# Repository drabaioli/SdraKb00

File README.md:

# SdraKb00

12 keys hot-swap macropad with rotary encoder.

## Assembled images

## Features

- 11 hot-swap keys
- Rotary encoder with push button
- AtMega32U4 MCU
- Per-key RGB led for backlighting
- USB-C connector
- On PCB SPI header
- MCU reset button
- Switch mounting plate
- Power LED indicator

## Keyboard Layout Editor link

[](http://www.keyboard-layout-editor.com/##@_backcolor=%23101C24&name=SdraKb00&author=drabaioli&switchMount=cherry&switchBrand=gateron&switchType=KS-3-Red&plate:true&pcb:false%3B&@_c=%23101C24&t=%2388FB7A%3B&=%3Ci%20class%2F='fa%20fa-fast-backward'%3E%3C%2F%2Fi%3E&=%3Ci%20class%2F='fa%20fa-play'%3E%3C%2F%2Fi%3E&=%3Ci%20class%2F='fa%20fa-fast-forward'%3E%3C%2F%2Fi%3E&_a:7&f:9%3B&=%3Ci%20class%2F='fa%20fa-circle-o-notch'%3E%3C%2F%2Fi%3E%3B&@_f:3%3B&=&=&=&_c=%2388FB7A&t=%23101C24%3B&=%3B&@_c=%23101C24&t=%2388FB7A&a:4%3B&=%3Ci%20class%2F='fa%20fa-chrome'%3E%3C%2F%2Fi%3E&=%3Ci%20class%2F='fa%20fa-terminal'%3E%3C%2F%2Fi%3E&=%3Ci%20class%2F='fa%20fa-youtube-play'%3E%3C%2F%2Fi%3E&=%3Ci%20class%2F='fa%20fa-spotify'%3E%3C%2F%2Fi%3E)

## Schematic

## PCB

## Switch plate

## Production files

The [production/](production/) folder contains files required for manufacturing the board, namely the [SdraKb00.zip](production/SdraKb00.zip) is an export (JLCPCB accepted format) of the gerber files and the [BOM](production/SdraKb00_bom.csv). The BOM was edited to add links to JLCPCB parts. Both files can be used to get the PCB manufactured by [JLCPCB](https://jlcpcb.com/) with relative components.

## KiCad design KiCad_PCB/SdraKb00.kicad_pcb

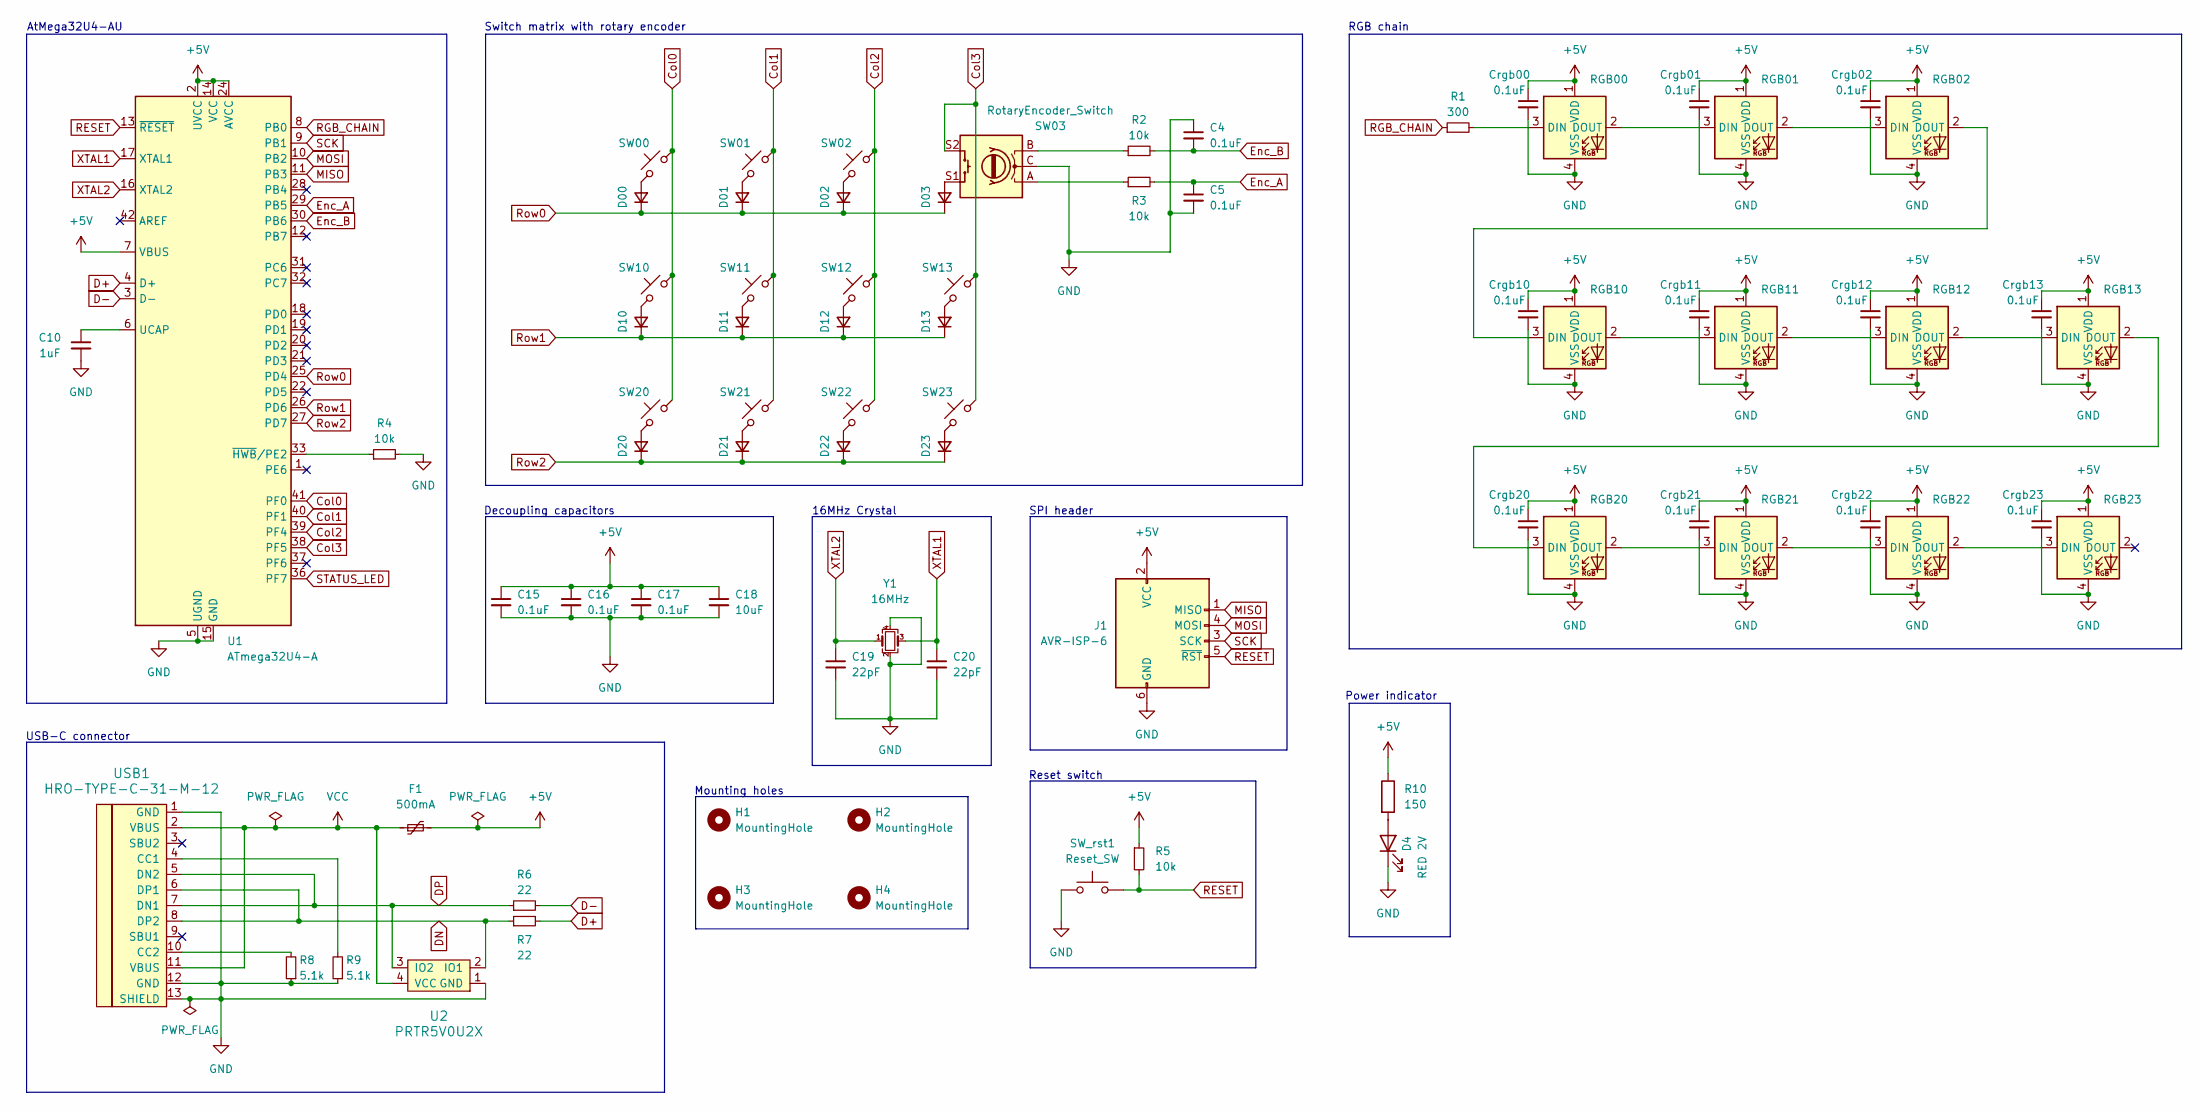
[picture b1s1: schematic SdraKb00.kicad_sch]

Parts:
C4, C5, C15, C16, C17: 0.1uF; C_0805_2012Metric_Pad1.18x1.45mm_HandSolder
C10: 1uF; C_0805_2012Metric_Pad1.18x1.45mm_HandSolder
C18: 10uF; C_0805_2012Metric_Pad1.18x1.45mm_HandSolder
C19, C20: 22pF; C_0805_2012Metric_Pad1.18x1.45mm_HandSolder
Crgb00, Crgb01, Crgb02, Crgb10, Crgb11, Crgb12, Crgb13, Crgb20, Crgb21, Crgb22, Crgb23: 0.1uF; C_0805_2012Metric_Pad1.18x1.45mm_HandSolder
D00, D01, D02, D03, D10, D11, D12, D13, D20, D21, D22, D23: D_Small; D_SOD-123
D4: RED 2V; LED_1206_3216Metric_Pad1.42x1.75mm_HandSolder
F1: 500mA; Fuse_1206_3216Metric_Pad1.42x1.75mm_HandSolder
H1, H2, H3, H4: MountingHole; MountingHole_3.2mm_M3
J1: AVR-ISP-6; PinHeader_1x06_P2.00mm_Horizontal
R1: 300; R_0805_2012Metric_Pad1.20x1.40mm_HandSolder
R2, R3, R4, R5: 10k; R_0805_2012Metric_Pad1.20x1.40mm_HandSolder
R6, R7: 22; R_0805_2012Metric_Pad1.20x1.40mm_HandSolder
R8, R9: 5.1k; R_0805_2012Metric_Pad1.20x1.40mm_HandSolder
R10: 150; R_0805_2012Metric_Pad1.20x1.40mm_HandSolder
RGB00, RGB01, RGB02, RGB10, RGB11, RGB12, RGB13, RGB20, RGB21, RGB22, RGB23: MX_SK6812MINI-E; LED_MX_6028R-ROT
SW00, SW01, SW02, SW10, SW11, SW12, SW13, SW20, SW21, SW22, SW23: SW_Push_45deg; SW_MX_HS_CPG151101S11_1u
SW03: RotaryEncoder_Switch; ROT_Alps_EC11E-Switch
SW_rst1: Reset_SW; SW_SPST_SKQG_WithStem
U1: ATmega32U4-A; TQFP-44_10x10mm_P0.8mm
U2: PRTR5V0U2X; SOT-143_Handsoldering
USB1: HRO-TYPE-C-31-M-12; HRO-TYPE-C-31-M-12-HandSoldering
Y1: 16MHz; Crystal_SMD_3225-4Pin_3.2x2.5mm_HandSoldering

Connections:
+5V: C15.1, C16.1, C17.1, C18.1, Crgb00.1, Crgb01.1, Crgb02.1, Crgb10.1, Crgb11.1, Crgb12.1, Crgb13.1, Crgb20.1, Crgb21.1, Crgb22.1, Crgb23.1, F1.2, J1.2 (VCC), R5.1, R10.1, RGB00.1 (VDD), RGB01.1 (VDD), RGB02.1 (VDD), RGB10.1 (VDD), RGB11.1 (VDD), RGB12.1 (VDD), RGB13.1 (VDD), RGB20.1 (VDD), RGB21.1 (VDD), RGB22.1 (VDD), RGB23.1 (VDD), U1.2 (UVCC), U1.7 (VBUS), U1.14 (VCC), U1.24 (AVCC), U1.34 (VCC), U1.44 (AVCC)
Col0: SW00.2, SW10.2, SW20.2, U1.41 (PF0)
Col1: SW01.2, SW11.2, SW21.2, U1.40 (PF1)
Col2: SW02.2, SW12.2, SW22.2, U1.39 (PF4)
Col3: SW03.S2, SW13.2, SW23.2, U1.38 (PF5)
D+: R7.2, U1.4 (D+)
D-: R6.2, U1.3 (D-)
DN: R7.1, U2.2 (IO1), USB1.6 (DP1), USB1.8 (DP2)
DP: R6.1, U2.3 (IO2), USB1.5 (DN2), USB1.7 (DN1)
Enc_A: C5.1, R3.2, U1.29 (PB5)
Enc_B: C4.2, R2.2, U1.30 (PB6)
GND: C4.1, C5.2, C10.2, C15.2, C16.2, C17.2, C18.2, C19.2, C20.2, Crgb00.2, Crgb01.2, Crgb02.2, Crgb10.2, Crgb11.2, Crgb12.2, Crgb13.2, Crgb20.2, Crgb21.2, Crgb22.2, Crgb23.2, D4.1 (K), J1.6 (GND), R4.2, R8.1, R9.1, RGB00.4 (VSS), RGB01.4 (VSS), RGB02.4 (VSS), RGB10.4 (VSS), RGB11.4 (VSS), RGB12.4 (VSS), RGB13.4 (VSS), RGB20.4 (VSS), RGB21.4 (VSS), RGB22.4 (VSS), RGB23.4 (VSS), SW03.C, SW_rst1.1, U1.5 (UGND), U1.15 (GND), U1.23 (GND), U1.35 (GND), U1.43 (GND), U2.1 (GND), USB1.1 (GND), USB1.12 (GND), USB1.13 (SHIELD), Y1.2, Y1.4
MISO: J1.1 (MISO), U1.11 (PB3)
MOSI: J1.4 (MOSI), U1.10 (PB2)
unnamed: D00.2 (A), SW00.1
unnamed: D01.2 (A), SW01.1
unnamed: D02.2 (A), SW02.1
unnamed: D03.2 (A), SW03.S1
unnamed: D4.2 (A), R10.2
unnamed: D10.2 (A), SW10.1
unnamed: D11.2 (A), SW11.1
unnamed: D12.2 (A), SW12.1
unnamed: D13.2 (A), SW13.1
unnamed: D20.2 (A), SW20.1
unnamed: D21.2 (A), SW21.1
unnamed: D22.2 (A), SW22.1
unnamed: D23.2 (A), SW23.1
unnamed: R2.1, SW03.B
unnamed: R3.1, SW03.A
unnamed: R1.2, RGB00.3 (DIN)
unnamed: RGB00.2 (DOUT), RGB01.3 (DIN)
unnamed: RGB01.2 (DOUT), RGB02.3 (DIN)
unnamed: RGB02.2 (DOUT), RGB10.3 (DIN)
unnamed: RGB10.2 (DOUT), RGB11.3 (DIN)
unnamed: RGB11.2 (DOUT), RGB12.3 (DIN)
unnamed: RGB12.2 (DOUT), RGB13.3 (DIN)
unnamed: RGB13.2 (DOUT), RGB20.3 (DIN)
unnamed: RGB20.2 (DOUT), RGB21.3 (DIN)
unnamed: RGB21.2 (DOUT), RGB22.3 (DIN)
unnamed: RGB22.2 (DOUT), RGB23.3 (DIN)
unnamed: C10.1, U1.6 (UCAP)
unnamed: R4.1, U1.33 (~HWB/PE2)
unnamed: R9.2, USB1.4 (CC1)
unnamed: R8.2, USB1.10 (CC2)
RESET: J1.5 (~RST), R5.2, SW_rst1.2, U1.13 (~RESET)
RGB_CHAIN: R1.1, U1.8 (PB0)
Row0: D00.1 (K), D01.1 (K), D02.1 (K), D03.1 (K), U1.25 (PD4)
Row1: D10.1 (K), D11.1 (K), D12.1 (K), D13.1 (K), U1.26 (PD6)
Row2: D20.1 (K), D21.1 (K), D22.1 (K), D23.1 (K), U1.27 (PD7)
SCK: J1.3 (SCK), U1.9 (PB1)
STATUS_LED: U1.36 (PF7)
VCC: F1.1, U2.4 (VCC), USB1.2 (VBUS), USB1.11 (VBUS)
XTAL1: C20.1, U1.17 (XTAL1), Y1.3
XTAL2: C19.1, U1.16 (XTAL2), Y1.1

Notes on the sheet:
USB-C connector
RGB chain
Reset switch
Mounting holes
Power indicator
SPI header
AtMega32U4-AU
Switch matrix with rotary encoder
16MHz Crystal
Decoupling capacitors

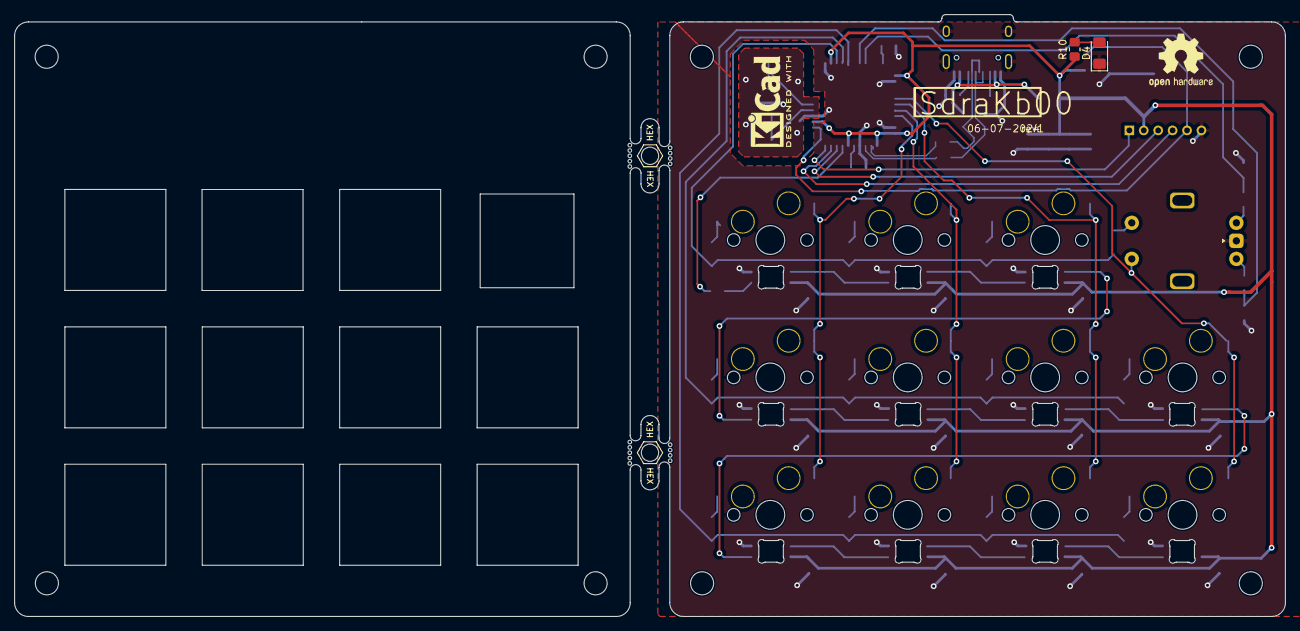
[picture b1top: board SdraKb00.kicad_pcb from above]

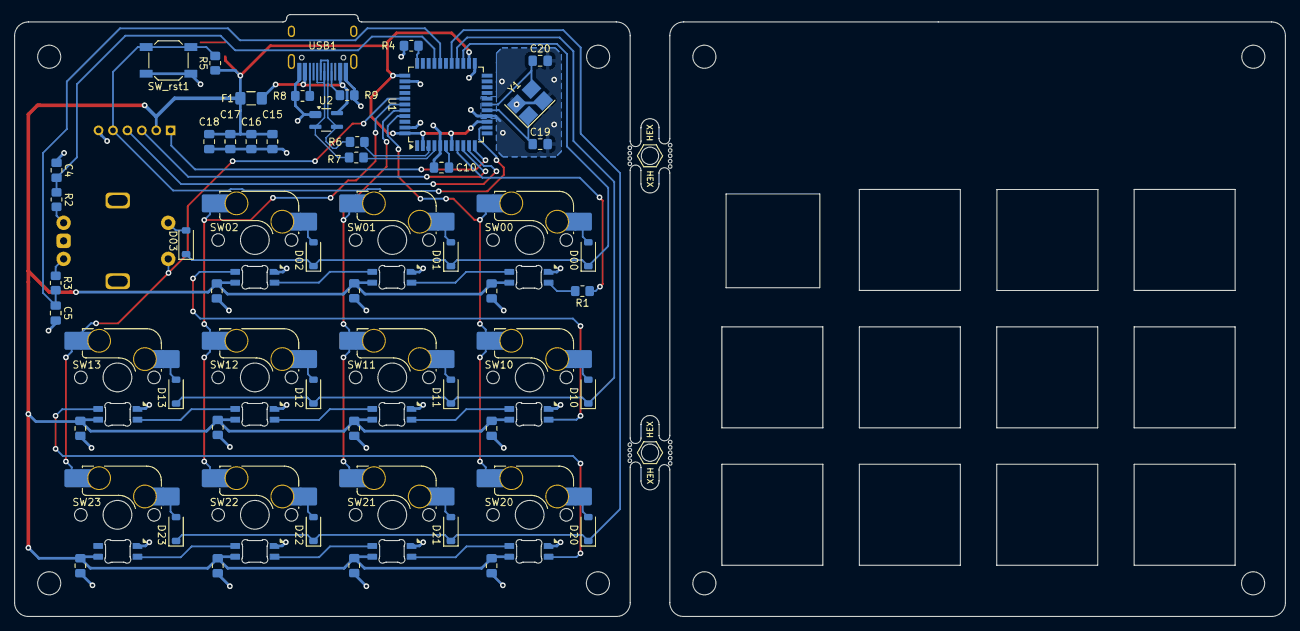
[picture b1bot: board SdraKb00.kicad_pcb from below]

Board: 2 copper layers, 176.1 x 83.4 mm, 95 parts (80 on the bottom side), 53 nets.

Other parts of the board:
H5, H6, H7, H8: MountingHole; MountingHole_3.2mm_M3
MB5, MB5#2: 5.5mm; mousebites_5p5mm_easysnap
SW00_cutout, SW01_cutout, SW02_cutout, SW10_cutout, SW11_cutout, SW12_cutout, SW13_cutout, SW20_cutout, SW21_cutout, SW22_cutout, SW23_cutout: SW_Push_45deg; SW_MX_HS_CPG151101S11_1u
SW03_cutout: RotaryEncoder_Switch; ROT_Alps_EC11E-Switch

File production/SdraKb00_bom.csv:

Id,Designator,Footprint,Quantity,Designation,Supplier and ref,Comment,LCSC link
1,R10,R_0805_2012Metric_Pad1.20x1.40mm_HandSolder,1,150,C410057,,https://www.lcsc.com/product-detail/Chip-Resistor-Surface-Mo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
2,SW03,ROT_Alps_EC11E-Switch,1,RotaryEncoder_Switch,C470742,,https://www.lcsc.com/product-detail/Rotary-Encoders_ALPSALPI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
3,D4,LED_1206_3216Metric_Pad1.42x1.75mm_HandSolder,1,RED 2V,C125086,,https://www.lcsc.com/product-detail/span-style-background-co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
4,J1,PinHeader_1x06_P2.00mm_Horizontal,1,AVR-ISP-6,C707009,,https://www.lcsc.com/product-detail/span-style-background-co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
5,"D20,D12,D01,D22,D03,D10,D02,D23,D21,D13,D00,D11",D_SOD-123,12,D_Small,C77978,,https://www.lcsc.com/product-detail/Switching-Diodes_MCC-Mic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
5,"SW22,SW01,SW01,SW01,SW01,SW01,SW01,SW12,SW11,SW01,SW13,SW01,SW20,SW23,SW01,SW01,SW01,SW10,SW01,SW02,SW21,SW00",SW_MX_HS_CPG151101S11_1u,11,SW_Push_45deg,C2803348,,https://www.lcsc.com/product-detail/Mechanical-Keyboard-Shaf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
7,"RGB22,RGB01,RGB21,RGB00,RGB11,RGB20,RGB10,RGB13,RGB02,RGB12,RGB23",LED_MX_6028R-ROT,11,MX_SK6812MINI-E,C5149201,,https://www.lcsc.com/product-detail/RGB-LEDs-Built-in-IC_OPS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
8,"Crgb23,C15,Crgb11,Crgb21,C4,Crgb00,Crgb13,Crgb22,C5,Crgb12,Crgb10,Crgb20,Crgb02,C17,Crgb01,C16",C_0805_2012Metric_Pad1.18x1.45mm_HandSolder,16,0.1uF,C730460,,https://www.lcsc.com/product-detail/Multilayer-Ceramic-Capac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
9,"C20,C19",C_0805_2012Metric_Pad1.18x1.45mm_HandSolder,2,22pF,C472837,,https://www.lcsc.com/product-detail/Multilayer-Ceramic-Capac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
10,"R6,R7",R_0805_2012Metric_Pad1.20x1.40mm_HandSolder,2,22,C413152,,https://www.lcsc.com/product-detail/Chip-Resistor-Surface-Mo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
11,F1,Fuse_1206_3216Metric_Pad1.42x1.75mm_HandSolder,1,500mA,C883126,,https://www.lcsc.com/product-detail/Resettable-Fuses_BHFUSE-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
12,"R8,R9",R_0805_2012Metric_Pad1.20x1.40mm_HandSolder,2,5.1k,C230649,,https://www.lcsc.com/product-detail/Chip-Resistor-Surface-Mo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
13,"R5,R4,R2,R3",R_0805_2012Metric_Pad1.20x1.40mm_HandSolder,4,10k,C180849,,https://www.lcsc.com/product-detail/Chip-Resistor-Surface-Mo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
14,C10,C_0805_2012Metric_Pad1.18x1.45mm_HandSolder,1,1uF,C2798196,,https://www.lcsc.com/product-detail/Multilayer-Ceramic-Capac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
15,Y1,Crystal_SMD_3225-4Pin_3.2x2.5mm_HandSoldering,1,16MHz,C5380579,,https://www.lcsc.com/product-detail/Crystals_JGHC-S321600022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
16,C18,C_0805_2012Metric_Pad1.18x1.45mm_HandSolder,1,10uF,C95841,,https://www.lcsc.com/product-detail/Multilayer-Ceramic-Capac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
17,SW_rst1,SW_SPST_SKQG_WithStem,1,Reset_SW,C116647,,https://www.lcsc.com/product-detail/Tactile-Switches_ALPSALP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
18,R1,R_0805_2012Metric_Pad1.20x1.40mm_HandSolder,1,300,C413174,,https://www.lcsc.com/product-detail/Chip-Resistor-Surface-Mo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
19,U1,TQFP-44_10x10mm_P0.8mm,1,ATmega32U4-A,C44854,,https://www.lcsc.com/product-detail/Microcontrollers-MCU-MPU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
20,USB1,HRO-TYPE-C-31-M-12-HandSoldering,1,HRO-TYPE-C-31-M-12,C165948,,https://www.lcsc.com/product-detail/USB-Type-C_Korean-Hropar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
21,U2,SOT-143_Handsoldering,1,PRTR5V0U2X,C5375321,,https://www.lcsc.com/product-detail/ESD-and-Surge-Protection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

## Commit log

2024-05-04 Setup project and submodules.
2024-05-10 Initial sketch based on jeremypaton (see link below)
    https://www.jeremypaton.com/2021/04/20/designing-a-custom-keyboard-pt-1/
2024-05-10 Ignoring KiCad tmp files.
2024-05-10 Ignoring KiCad tmp files. (#1)
2024-05-10 Fixing library paths.
2024-05-10 Adjusted first sketch based on masterzen.
    https://www.masterzen.fr/2020/05/03/designing-a-keyboard-part-1/
2024-05-10 Adding layout image to readme.
2024-05-12 Replaced AtMega32U4 with default library. Adding switch array.
2024-05-12 Adding RGB chain.
2024-05-12 Adding mounting holes.
2024-05-12 Readme.
2024-05-12 Repo setup (#2)
    * Setup project and submodules.
    * Initial sketch based on jeremypaton (see link below)
    https://www.jeremypaton.com/2021/04/20/designing-a-custom-keyboard-pt-1/
    * Fixing library paths.
    * Adjusted first sketch based on masterzen.
    https://www.masterzen.fr/2020/05/03/designing-a-keyboard-part-1/
2024-05-14 First round assigning footprints.
2024-05-19 Complete footprint assignment.
    - Removed unused submodules
    - Adding marbastlib submodule
2024-05-19 Assign footprints (#3)
    * First round assigning footprints.
    * Complete footprint assignment.
    - Removed unused submodules
    - Adding marbastlib submodule
2024-05-20 Aligning SWs, Ds, LEDs.
2024-05-25 Placing all components before routing.
2024-05-25 More wiring.
2024-05-26 More PCB routing.
2024-06-02 Routing MCU powerlines, Crystal ground zone.
2024-06-10 Finish routing power.
2024-06-10 Routing switch matrix.
2024-06-10 Cutting rounded corner edges.
2024-06-11 Improving silk screen placement.
2024-07-05 Finilizing PCB design.
2024-07-05 Pcb design (#4)
    * Aligning SWs, Ds, LEDs.
    * Placing all components before routing.
    * More wiring.
    * More PCB routing.
    * Routing MCU powerlines, Crystal ground zone.
    * Finish routing power.
2024-07-06 Adding initial silkscreen.
2024-07-06 Adding KiCad & OpenHW logos.
2024-07-06 Silkscreen (#5)
    * Adding initial silkscreen.
    * Adding KiCad & OpenHW logos.
2024-07-06 Adding PCB renders.
2024-07-06 Adding PCB renders. (#6)
2024-07-10 Adding power indicator LED.
2024-07-10 Re-placing silkscreen.
2024-07-10 Adding power indicator LED (#7)
    * Adding power indicator LED.
    * Re-placing silkscreen.
2024-07-20 Adding switch mounting plate.
2024-07-20 Mounting plate (#8)
    * Adding power indicator LED.
    * Re-placing silkscreen.
    * Adding switch mounting plate.
2024-07-21 Adding 3D model for reset button.
2024-07-21 Adding back render.
2024-07-21 Adding 3D model for reset button (#9)
    * Adding 3D model for reset button.
    * Adding back render.
2024-07-26 Changing power indicator specs.
2024-07-26 Changing power indicator specs. (#10)
2024-08-03 Adding gerber files and BOM.
2024-08-03 Adding (ignored) bom.
2024-08-03 Production files (#11)
    * Adding gerber files and BOM.
    * Adding (ignored) bom.
2024-09-20 Adding assembled result images.
2024-09-20 Adding assembled result images. (#17)
2025-07-21 Adding "Building the SdraKb00 macropad" YouTube video.
2025-07-21 Adding YouTube logo overlay to thumbnail.
2025-07-21 Adding the actual thumbnail.
2025-07-21 Youtube link (#18)
    * Adding "Building the SdraKb00 macropad" YouTube video.
    * Adding YouTube logo overlay to thumbnail.
    * Adding the actual thumbnail.
